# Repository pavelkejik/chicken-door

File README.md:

# 🐔 Automated Chicken Coop Ecosystem  
_A modular IoT platform for stress-free backyard chicken keeping_

## Contents
1. [Project Overview](#project-overview)  
2. [Core Features](#core-features)  
3. [System Architecture](#system-architecture)  
4. [Hardware](#hardware)  
   1. [Chicken Door (Gateway)](#chicken-door-gateway)  
   2. [Accessories](#accessories)  
5. [Communication & APIs](#communication--apis)  
6. [Safety & Reliability](#safety--reliability)  
7. [Getting Started](#getting-started)  
8. [MQTT Quick Reference](#mqtt-quick-reference)  
9. [Roadmap](#roadmap)  

---

## Project Overview
The project automates everyday coop duties by combining a **smart sliding door**, a set of battery-powered **accessories** (feeder, camera, …) and a modern web UI.  
The door acts as the **gateway**: it drives the motor, pairs with accessories over low-power **ESP-NOW**, exposes a local **Web UI + HTTP API**, and bridges everything to standard **MQTT** and optional **Modbus RTU** for seamless Home-Assistant integration.

---

## Core Features
| Area | Highlights |
|------|------------|
|Automation|• Auto-open/close by **sunrise/sunset** (astronomical) or **ambient light** plus configurable offsets  <br>• Full manual override via button, Web UI, MQTT, or Modbus|
|Safety|• Encoder-based position tracking, upper/lower limit calibration, soft-start/stop  <br>• Stall/over-current detection, timeout watchdog, emergency-stop state|
|Connectivity|• Wi-Fi STA/AP, **ESP-NOW** for accessories (1 km LR)  <br>• MQTT (via configurable `base_topic`), HTTP/REST, captive portal|
|Updates|• **OTA** firmware & file-system updates for door *and* every paired accessory through ESP-NOW|
|Accessories|• **Smart Feeder** – scheduled or weight-based servings  <br>• **Coop Camera** – still images on demand  <br>_Add your own!_  |
|Power|Door on 12 V DC; accessories battery-powered for months thanks to deep-sleep design|

---

## System Architecture
```
ESP32-S3 Door  ── Wi-Fi STA ⇆ Home Network ⇆ MQTT Broker / Home Assistant
      │
      ├─ Wi-Fi AP (for first-run config)
      └─ ESP-NOW P2P
             ├─ Feeder (ESP32-C3, battery)
             └─ Camera (ESP32-S3, battery)
```
Door firmware is C++/Arduino on FreeRTOS; the web interface is Vite + Vue 3 + Vuetify served directly from on-board **LittleFS**.

---

## Hardware
### Chicken Door (Gateway)
* **Drive**: 12 V DC gear-motor + rack-and-pinion (self-locking)  
* **MCU**: ESP32-S3-WROOM-1 (8 MB PSRAM)  
* **Sensors**: quadrature encoder, NTC temperature, photodiode (light)  
* **IO Expansion**: 2 GPIO inputs, open-collector output, RS-485 (Modbus RTU)  
* **Indicators**: bi-color status LED

### Accessories
| Name | Repo | Brief |
|------|------|-------|
|Smart Feeder|<https://github.com/pavelkejik/chicken-feeder>|Servo-lid + load-cell; daily schedule or “feed-to-weight” mode|
|Coop Camera|<https://github.com/pavelkejik/chicken-camera>|ESP32-S3 w/ OV2640; images send over ESP-NOW|

Each accessory ships its own OTA-updatable firmware and pairs with one click via the Web UI. Status appears alongside the door dashboard.

---

## Communication & APIs
| Layer | Tech | Notes |
|-------|------|-------|
|Local Web UI|`http://dvirka.local` (mDNS) or captive portal |Full config, live telemetry, manual commands|
|REST/JSON|`/api/door`, `/api/accessory/{id}`|Same parameter map as MQTT|
|MQTT|`<base_topic>/state/...` and `/set/...` |Door & all accessories share a unified schema|
|Modbus RTU|RS-485, 9600 8N1 |Minimal register map for industrial PLCs|
|ESP-NOW|1 Mbit/s (500 kbit/s LR) |door = server, accessories = clients|

---

## Safety & Reliability
* **Hard limits + soft position** ensure gentle landings and no unexpected slams.  
* Every motion path is guarded by current & timeout watchdogs; any fault triggers _Emergency Stop_ with MQTT/HTTP event.  
* Door refuses to auto-close if position => `UNKNOWN` until next recalibration pass.  
* Accessories inherit door time-base and watchdog pings to detect battery loss.

---

## Getting Started
### 1. Flash Firmware
```bash
# Door
cd firmware/door
pio run -t upload         # USB
pio run -t uploadfs       # Web assets
# Feeder / Camera similar...
```

### 2. First Boot & Wi-Fi Join
1. Hold the door’s button >3 s → it starts `Dvirka` AP (both LEDs solid).  
2. Connect with a phone, open any page → captive portal shows config.  
3. Enter your SSID/PSK; the door reboots and joins STA mode.  

### 3. Build the Web UI Locally (optional)
```bash
cd web-ui
npm i
npm run dev
```

### 4. Pair Accessories
Open **Menu → Accessories → “New” → Pair** and press the accessory button once. State flips from _New_ → _Connected_.

---

## MQTT Quick Reference
```text
<base_topic>/state/position        = "OPEN" | "CLOSED" | "OPENING" | ...
<base_topic>/state/light_lux       = 123
<base_topic>/set/command           ← "OPEN" | "CLOSE" | "STOP"

<base_topic>/devices/<id>/state/weight_g
```
Replace `<base_topic>` in the Web UI.

---

## Roadmap
- [ ] Add waterer accessory
- [ ] Implement chicken presence counting using RFID tags   
- [x] Publish 3D-print STLs & KiCad sources

---

### Author
**Pavel Kejík**

> Built for my family’s coop, released for every backyard chicken keeper 🤘

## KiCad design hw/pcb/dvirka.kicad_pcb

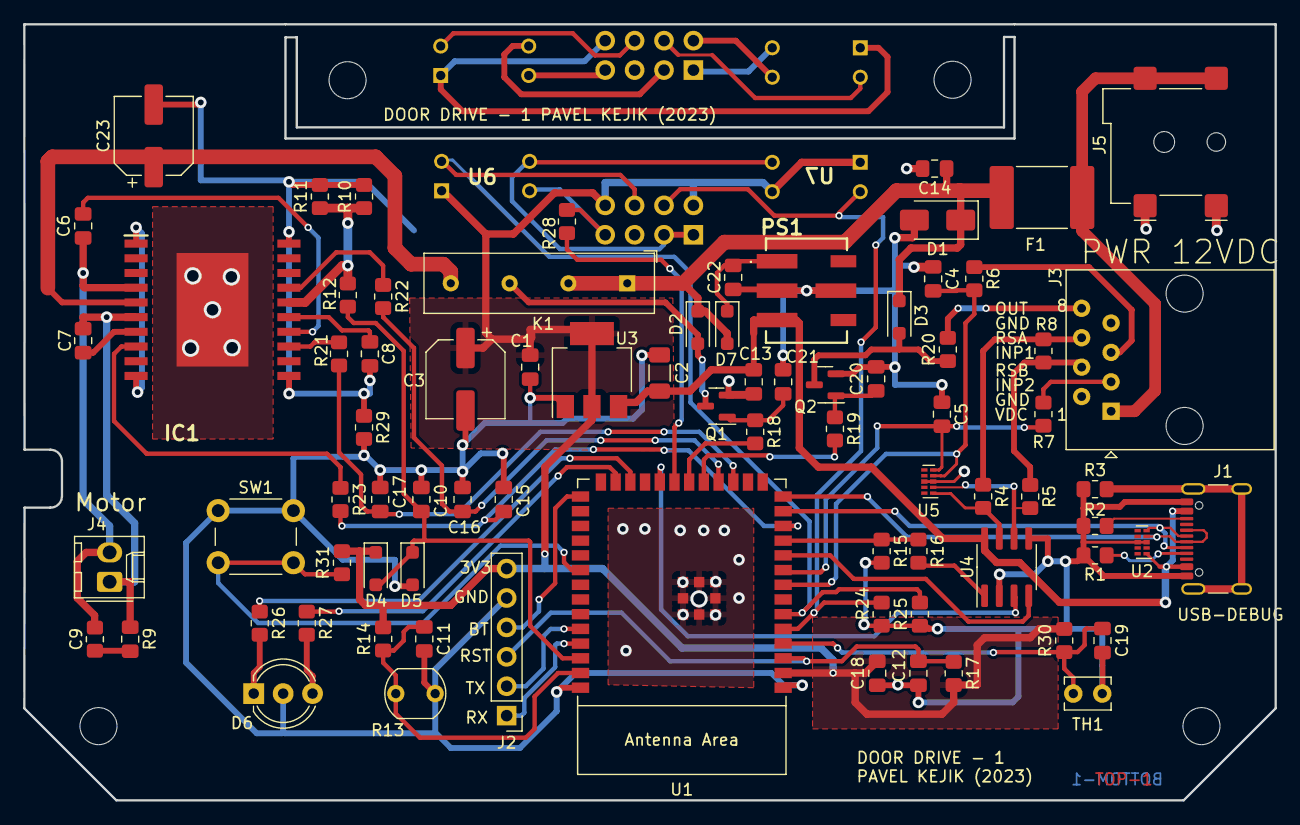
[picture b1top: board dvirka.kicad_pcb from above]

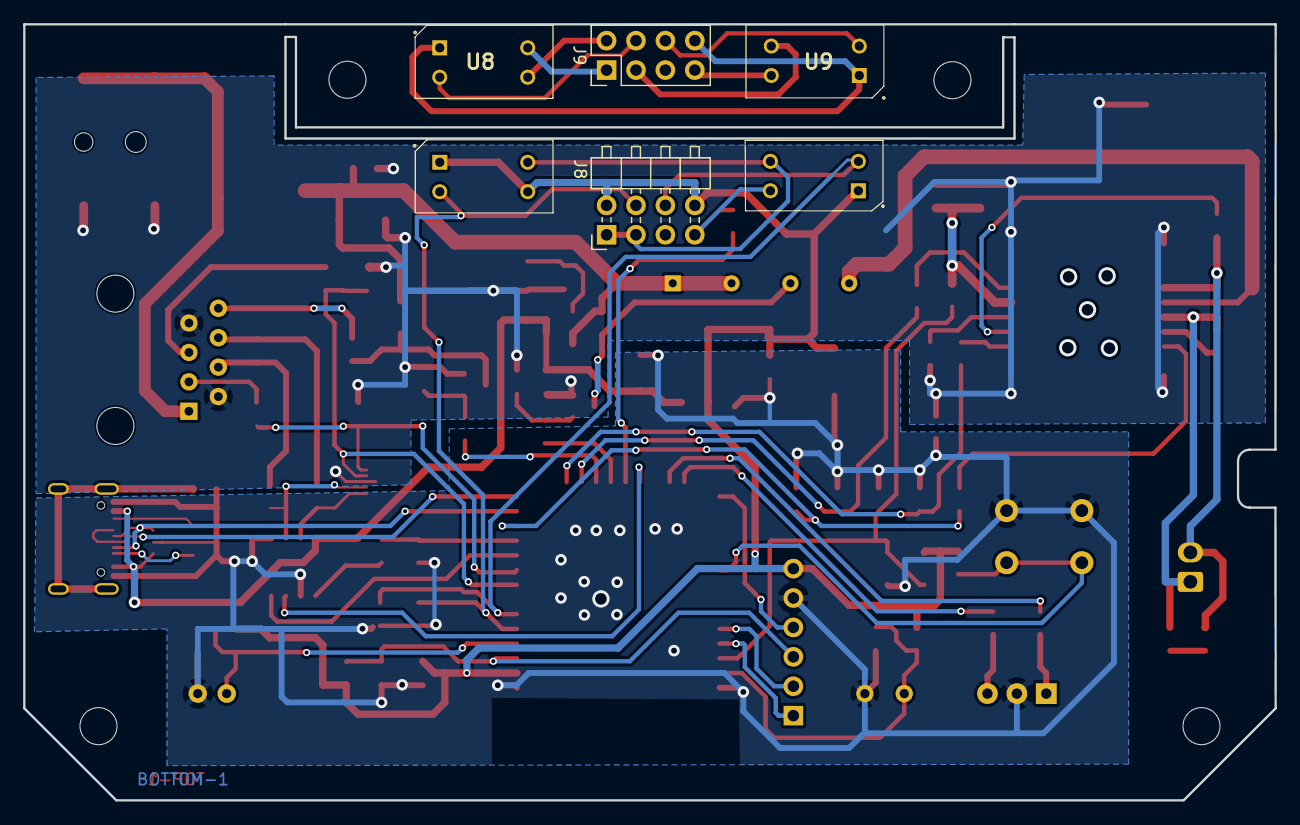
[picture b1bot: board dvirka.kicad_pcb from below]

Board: 2 copper layers, 108.1 x 67.0 mm, 85 parts (6 on the bottom side), 69 nets.

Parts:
C1, C4, C5, C14: 100nF; C_0805_2012Metric_Pad1.18x1.45mm_HandSolder
C2: 10u/50V; C_1206_3216Metric_Pad1.33x1.80mm_HandSolder
C3, C23: 150uF/16V; CP_Elec_6.3x7.7
C6, C7, C9, C10, C18, C20, C21: 15nF; C_0805_2012Metric_Pad1.18x1.45mm_HandSolder
C8: 220nF; C_0805_2012Metric_Pad1.18x1.45mm_HandSolder
C11, C12, C19: 1nF; C_0805_2012Metric_Pad1.18x1.45mm_HandSolder
C13, C22: 10uF; C_0805_2012Metric_Pad1.18x1.45mm_HandSolder
C15, C16, C17: 33pF; C_0805_2012Metric_Pad1.18x1.45mm_HandSolder
D1: ESDA18-1K; D_SMA
D2, D3, D4, D5: 1N4148WT; D_SOD-123F
D6: LED_Dual_AKA; LED_D5.0mm-3
D7: 1N4007; D_SOD-123F
F1: 0ZCF0100AF2A; Fuse_2920_7451Metric_Pad2.10x5.45mm_HandSolder
IC1: L6201PS; SOIC127P1420X360-21N
J1: USB_C_Receptacle_USB2.0; USB_C_Receptacle_GCT_USB4105-xx-A_16P_TopMnt_Horizontal
J2: Conn_01x06_Socket; PinHeader_1x06_P2.54mm_Vertical
J3: RJ45; RJ45_Amphenol_54602-x08_Horizontal
J4: Conn_01x02_Pin; Molex_KK-254_AE-6410-02A_1x02_P2.54mm_Vertical
J5: Barrel_Jack_Switch; BarrelJack_Wuerth_694108106102_2.5x5.5mm
J8: Conn_02x04_Odd_Even; PinHeader_2x04_P2.54mm_Horizontal
J9: Conn_02x04_Odd_Even; PinHeader_2x04_P2.54mm_Vertical
K1: SILxx-1Axx-71x; Relay_SPST_StandexMeder_SIL_Form1A
PS1: K7805MT-500R4; K7805MT500R4
Q1, Q2: BC846; SOT-23
R1, R2, R9: 5k1; R_0805_2012Metric_Pad1.20x1.40mm_HandSolder
R3, R17: 1M; R_0805_2012Metric_Pad1.20x1.40mm_HandSolder
R4, R5: 10R; R_0805_2012Metric_Pad1.20x1.40mm_HandSolder
R6, R7, R26, R27: 470R; R_0805_2012Metric_Pad1.20x1.40mm_HandSolder
R8, R20: 120R; R_0805_2012Metric_Pad1.20x1.40mm_HandSolder
R10, R11: 3R3; R_0805_2012Metric_Pad1.20x1.40mm_HandSolder
R12: 4K7; R_0805_2012Metric_Pad1.20x1.40mm_HandSolder
R13: R_Photo; R_LDR_5.1x4.3mm_P3.4mm_Vertical
R14, R31: 100K; R_0805_2012Metric_Pad1.20x1.40mm_HandSolder
R15: 3K3; R_0805_2012Metric_Pad1.20x1.40mm_HandSolder
R16, R24, R25: 2K2; R_0805_2012Metric_Pad1.20x1.40mm_HandSolder
R18, R19, R30: 10K; R_0805_2012Metric_Pad1.20x1.40mm_HandSolder
R21, R22, R23: 100R; R_0805_2012Metric_Pad1.20x1.40mm_HandSolder
R28: 68R; R_0805_2012Metric_Pad1.20x1.40mm_HandSolder
R29: 0R; R_0805_2012Metric_Pad1.20x1.40mm_HandSolder
SW1: SW_Push; SW_PUSH_6mm
TH1: Thermistor_NTC; C_Disc_D3.8mm_W2.6mm_P2.50mm
U1: ESP32-S3-WROOM-1
U2, U5: TPD4E02B04DQA; USON-10_2.5x1.0mm_P0.5mm
U3: AMS1117-3.3; SOT-223-3_TabPin2
U4: MAX485E; SOIC-8_3.9x4.9mm_P1.27mm
U6, U7, U8, U9: TCST1103

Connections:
+3.3V: C1.1, C3.1, C18.2, D4.1 (K), J2.6, J8.2, J8.8, R14.2, R17.2, R30.2, R31.2, U1.2 (3V3), U3.2 (VO), U6.1 (+_1), U7.1 (+_1), U7.3 (+_2)
+5V: C2.1, C13.1, J1.A4 (VBUS), J1.A9 (VBUS), J1.B4 (VBUS), J1.B9 (VBUS), PS1.3 (+VO), U2.1 (IO1), U3.3 (VI), U4.8 (VCC)
+12V: C14.1, D1.1 (K), D2.1 (K), D3.1 (K), D7.2 (A), F1.2, K1.1, K1.3
AINP_MOT: C10.2, D4.2 (A), D5.1 (K), R12.1, U1.38 (GPIO2/TOUCH2/ADC1_CH1)
AINP_PHOTO: C11.1, R13.1, R14.1, U1.39 (GPIO1/TOUCH1/ADC1_CH0)
AINP_THERM: C19.1, R30.1, TH1.1, U1.4 (GPIO4/TOUCH4/ADC1_CH3)
AUXOUT: J3.8, R20.2
BOOT: J2.4, U1.27 (GPIO0/BOOT)
DE485: U1.22 (GPIO14/TOUCH14/ADC2_CH3/FSPIWP/FSPIDQS/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), U4.3 (DE)
DEBUG_RX: J2.1, U1.37 (U0TXD/GPIO43/CLK_OUT1)
DEBUG_TX: J2.2, U1.36 (U0RXD/GPIO44/CLK_OUT2)
GND: C1.2, C2.2, C3.2, C10.1, C11.2, C12.1, C15.2, C16.2, C17.1, C18.1, C19.2, D5.2 (A), D6.2 (K), J1.A1 (GND), J1.A12 (GND), J1.B1 (GND), J1.B12 (GND), J2.5, R1.2, R2.2, R3.1, R13.2, R15.2, R24.1, R25.1, R29.2, SW1.1, TH1.2, U1.1 (GND), U1.40 (GND), U1.41 (GND), U2.3 (G), U2.8 (G), U3.1 (GND), U4.2 (~RE), U4.5 (GND)
GNDPWR: C4.1, C5.1, C8.1, C13.2, C14.2, C20.2, C21.2, C22.2, C23.2, D1.2 (A), IC1.1 (GND_1), IC1.10 (GND_2), IC1.11 (GND_3), IC1.20 (GND_4), J3.2, J3.7, J5.1, PS1.2 (GND_1), PS1.5 (GND_2), Q1.2 (E), Q2.2 (E), R10.2, R11.2, R29.1, U5.3 (G), U5.8 (G)
INP1: C4.2, R6.2, U1.8 (GPIO15/U0RTS/ADC2_CH4/XTAL_32K_P), U5.4 (IO3)
INP2: C5.2, R7.2, U1.9 (GPIO16/U0CTS/ADC2_CH5/XTAL_32K_N), U5.5 (IO4)
INP_ENCA: J8.4, R24.2, U1.5 (GPIO5/TOUCH5/ADC1_CH4), U7.2 (E)
INP_ENCB: J8.6, R25.2, U1.6 (GPIO6/TOUCH6/ADC1_CH5), U6.2 (E)
MOT_PWR: C23.1, IC1.5 (VS), K1.7
unnamed: C9.1, R9.2
unnamed: D2.2 (A), K1.5, Q1.3 (C)
unnamed: D3.2 (A), Q2.3 (C), R20.1
unnamed: D6.1 (A1), R26.2
unnamed: D6.3 (A2), R27.2
unnamed: C22.1, D7.1 (K), PS1.1 (+VIN)
unnamed: C7.2, IC1.7 (BOOT1)
unnamed: C6.2, IC1.14 (BOOT2)
unnamed: IC1.17 (ENABLE), R22.1
unnamed: IC1.8 (IN1), R23.1
unnamed: IC1.13 (IN2), R21.1
unnamed: C7.1, C9.2, IC1.6 (OUT1), J4.1
unnamed: C6.1, IC1.4 (OUT2), J4.2, R9.1
unnamed: IC1.16 (SENSE), R10.1, R11.1, R12.2
unnamed: C8.2, IC1.15 (VREF)
unnamed: J1.A5 (CC1), R1.1
unnamed: J1.B5 (CC2), R2.1
unnamed: J1.S1 (SHIELD), R3.2
unnamed: J3.3, R7.1
unnamed: J3.4, R5.1, R8.2
unnamed: J3.5, R6.1
unnamed: J3.6, R4.1, R8.1
unnamed: J8.1, J8.3, U6.3 (+_2), U7.4 (D)
unnamed: J8.7, R28.2, U6.4 (D)
unnamed: J9.1, U8.4 (D)
unnamed: J9.2, U8.3 (+_2)
unnamed: J9.3, U9.3 (+_2)
unnamed: J9.4, U8.2 (E)
unnamed: J9.6, U9.2 (E)
unnamed: J9.7, U9.4 (D)
unnamed: J9.8, U8.1 (+_1), U9.1 (+_1)
unnamed: C21.1, Q1.1 (B), R18.1
unnamed: C20.1, Q2.1 (B), R19.1
unnamed: R31.1, SW1.2, U1.32 (MTCK/GPIO39/CLK_OUT3/SUBSPICS1)
unnamed: R5.2, U4.6 (A), U5.2 (IO2)
unnamed: R4.2, U4.7 (B), U5.1 (IO1)
unnamed: R16.2, U4.1 (RO)
OUT_AUXOUT: R19.2, U1.19 (GPIO11/TOUCH11/ADC2_CH0/FSPID/FSPIIO5/S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)
OUT_ENC: R28.1, U1.21 (GPIO13/TOUCH13/ADC2_CH2/FSPIQ/FSPIIO7/S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)
OUT_LEDG: R27.1, U1.25 (GPIO48/SPICLK_N/SUBSPICLK_N_DIFF)
OUT_LEDR: R26.1, U1.24 (GPIO47/SPICLK_P/SUBSPICLK_P_DIFF)
OUT_MOT1: C15.1, R23.2, U1.12 (GPIO8/TOUCH8/ADC1_CH7/SUBSPICS1)
OUT_MOT2: C17.2, R21.2, U1.17 (GPIO9/TOUCH9/ADC1_CH8/FSPIHD/SUBSPIHD)
OUT_MOT_EN: C16.1, R22.2, U1.18 (GPIO10/TOUCH10/ADC1_CH9/FSPICS0/FSPIIO4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)
OUT_MOT_PWR: R18.2, U1.20 (GPIO12/TOUCH12/ADC2_CH1/FSPICLK/FSPIIO6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)
RESET: C12.2, J2.3, R17.1, U1.3 (EN)
RXD485: R15.1, R16.1, U1.11 (GPIO18/U1RXD/ADC2_CH7/CLK_OUT3)
TXD485: U1.10 (GPIO17/U1TXD/ADC2_CH6), U4.4 (DI)
USBDATA+: J1.A6 (D+), J1.B6 (D+), U1.14 (GPIO20/U1CTS/ADC2_CH9/CLK_OUT1/USB_D+), U2.4 (IO3)
USBDATA-: J1.A7 (D-), J1.B7 (D-), U1.13 (GPIO19/U1RTS/ADC2_CH8/CLK_OUT2/USB_D-), U2.5 (IO4)
VDC: F1.1, J3.1, J5.2, J5.3

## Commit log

2025-03-02 Initial commit of chicken door project
2025-04-23 Add README and implement Modbus communication enhancements
2025-04-23 Publish 3D-print STLs & KiCad sources
2025-05-16 Add support for AI egg counting camera
